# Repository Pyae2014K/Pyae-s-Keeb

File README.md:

# Pyae-s-Keeb

My Keeb is a 75% keyboard with a knob and via support.
The firmware was built with QMK.

It serves as a keyboard that I can use every day to type and play games.

## Features:
- EC11 Rotary Encoder for Volume
- 82 Switches for the keys
- [VIA](https://www.caniusevia.com/) support

## PCB
My PCB was made in KiCad.

Schematic

PCB

I used [Joe Scotto's](https://www.youtube.com/@joe_scotto) footprints for most of the components.

## CAD Model
Everyting fits together using 8 M3 Screws and Heatset inserts.

It has 2 different pieces, the Case

and the Plate

## Firmware
This Keeb uses [QMK](https://qmk.fm/) firmware for the code.
-82 Switches for keys
-Rotary encoder for volume

## Bom:
Here is everything needed to make my Keeb

82x Cherry MX Switches
82x DSA Keycaps
8x M3x5x4 Heatset inserts
8x M3x18mm SHCS Bolts
83x 1N4148 DO-35 Diodes.
1x EC11 Rotary Encoder
1x Raspberry Pi Pico
1x Case (2 printed parts)

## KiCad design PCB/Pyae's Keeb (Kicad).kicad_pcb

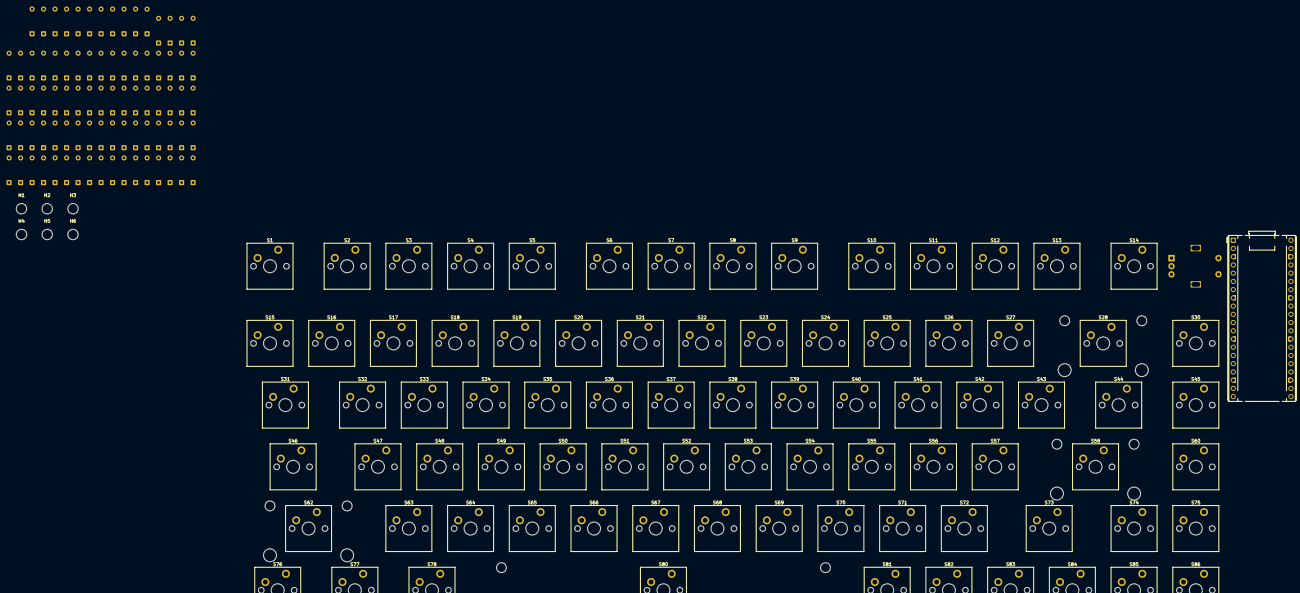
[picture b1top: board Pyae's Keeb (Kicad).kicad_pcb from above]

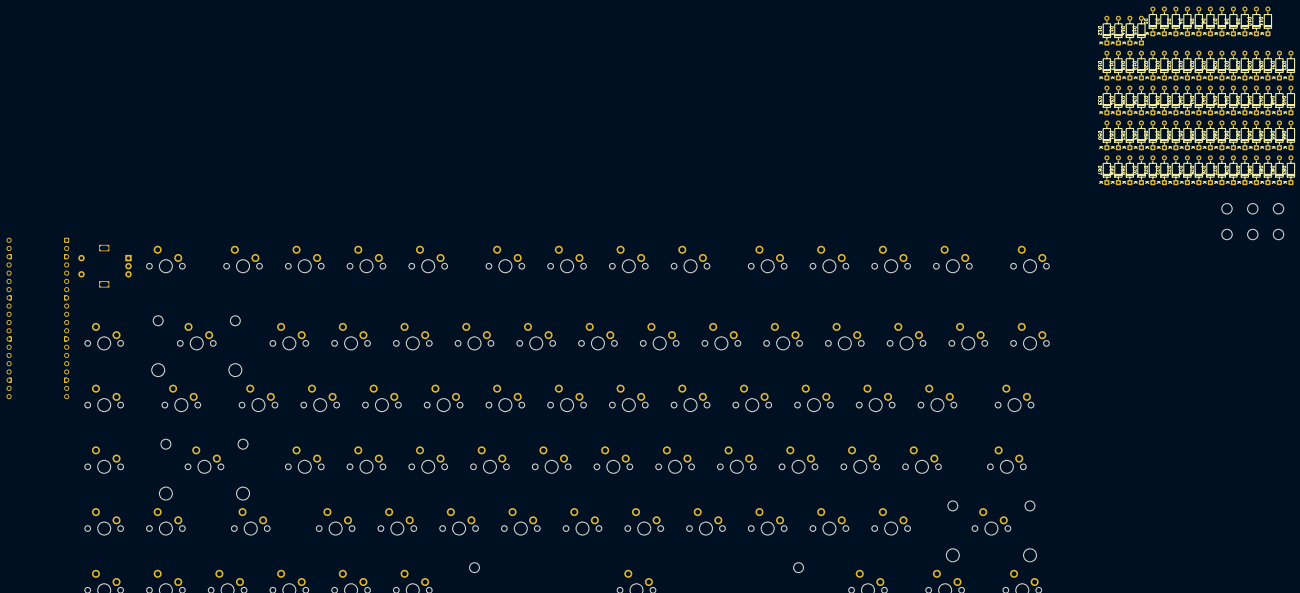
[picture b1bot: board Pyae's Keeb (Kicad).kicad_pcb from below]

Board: 2 copper layers, 177 parts (83 on the bottom side), 107 nets, no tracks yet.

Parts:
A1: RaspberryPi_Pico; RaspberryPi_Pico_Common_THT
D1, D2, D3, D4, D5, D6, D7, D8, D9, D10, D11, D12, D13, D14, D15, D16, D17, D18, D19, D20, D21, D22, D23, D24, D25, D26, D27, D28, D29, D30, D31, D32, D33, D34, D35, D36, D37, D38, D39, D40, D41, D42, D43, D44, D45, D46, D47, D48, D49, D50, D51, D52, D53, D54, D55, D56, D57, D58, D59, D60, D61, D62, D63, D64, D65, D66, D67, D68, D69, D70, D71, D72, D73, D74, D75, D76, D77, D78, D79, D80, D81, D82, D83: D_DO-35_SOD27_P7.62mm_Horizontal
H1, H2, H3, H4, H5, H6: MountingHole; MountingHole_3.2mm_M3
S1, S2, S3, S4, S5, S6, S7, S8, S9, S10, S11, S12, S13, S14, S15, S16, S17, S18, S19, S20, S21, S22, S23, S24, S25, S26, S27, S28, S30, S32, S33, S34, S35, S36, S37, S38, S39, S40, S41, S42, S43, S45, S47, S48, S49, S50, S51, S52, S53, S54, S55, S56, S57, S58, S60, S62, S63, S64, S65, S66, S67, S68, S69, S70, S71, S72, S74, S75, S80, S81, S82, S83, S84, S85, S86: MX_PCB_1.00u
S29: MX_stab; STAB_MX_2u
S31, S44: MX_PCB_1.50u
S46, S73: MX_PCB_1.75u
S59, S61: MX_stab; STAB_MX_2.25u
S76, S77, S78: MX_PCB_1.25u
S79: MX_stab; STAB_MX_6.25u
SW1: RotaryEncoder_Switch; Encoder_EC11_MX

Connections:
Col0: A1.1 (GPIO0), S1.1, S15.1, S31.1, S46.1, S62.1, S76.1
Col1: A1.2 (GPIO1), S2.1, S16.1, S32.1, S47.1, S63.1, S77.1
Col2: A1.4 (GPIO2), S3.1, S17.1, S33.1, S48.1, S64.1, S78.1
Col3: A1.5 (GPIO3), S4.1, S18.1, S34.1, S49.1, S65.1
Col4: A1.6 (GPIO4), S5.1, S19.1, S35.1, S50.1, S66.1
Col5: A1.7 (GPIO5), S6.1, S20.1, S36.1, S51.1, S67.1, S80.1
Col6: A1.9 (GPIO6), S7.1, S21.1, S37.1, S52.1, S68.1
Col7: A1.10 (GPIO7), S8.1, S22.1, S38.1, S53.1, S69.1
Col8: A1.11 (GPIO8), S9.1, S23.1, S39.1, S54.1, S70.1, S81.1
Col9: A1.12 (GPIO9), S10.1, S24.1, S40.1, S55.1, S71.1, S82.1
Col10: A1.14 (GPIO10), S11.1, S25.1, S41.1, S56.1, S72.1, S83.1
Col11: A1.15 (GPIO11), S12.1, S26.1, S42.1, S57.1, S73.1, S84.1
Col12: A1.16 (GPIO12), S13.1, S27.1, S43.1, S58.1, S74.1, S85.1
Col13: A1.17 (GPIO13), S14.1, S28.1, S44.1
Col14: A1.19 (GPIO14), S30.1, S45.1, S60.1, S75.1, S86.1, SW1.S1
GND: A1.3 (GND), A1.8 (GND), A1.13 (GND), A1.18 (GND), A1.23 (GND), A1.28 (GND), A1.38 (GND), SW1.C
unnamed: D67.2 (A), S1.2
unnamed: D68.2 (A), S15.2
unnamed: D69.2 (A), S31.2
unnamed: D70.2 (A), S46.2
unnamed: D71.2 (A), S62.2
unnamed: D72.2 (A), S76.2
unnamed: D73.2 (A), S2.2
unnamed: D74.2 (A), S16.2
unnamed: D75.2 (A), S32.2
unnamed: D76.2 (A), S47.2
unnamed: D77.2 (A), S63.2
unnamed: D78.2 (A), S77.2
unnamed: D79.2 (A), S3.2
unnamed: D80.2 (A), S17.2
unnamed: D81.2 (A), S33.2
unnamed: D82.2 (A), S48.2
unnamed: D83.2 (A), S64.2
unnamed: D50.2 (A), S78.2
unnamed: D51.2 (A), S4.2
unnamed: D52.2 (A), S18.2
unnamed: D53.2 (A), S34.2
unnamed: D54.2 (A), S49.2
unnamed: D55.2 (A), S65.2
unnamed: D56.2 (A), S5.2
unnamed: D57.2 (A), S19.2
unnamed: D58.2 (A), S35.2
unnamed: D59.2 (A), S50.2
unnamed: D60.2 (A), S66.2
unnamed: D61.2 (A), S6.2
unnamed: D62.2 (A), S20.2
unnamed: D63.2 (A), S36.2
unnamed: D64.2 (A), S51.2
unnamed: D65.2 (A), S67.2
unnamed: D66.2 (A), S80.2
unnamed: D33.2 (A), S7.2
unnamed: D34.2 (A), S21.2
unnamed: D35.2 (A), S37.2
unnamed: D36.2 (A), S52.2
unnamed: D37.2 (A), S68.2
unnamed: D38.2 (A), S8.2
unnamed: D39.2 (A), S22.2
unnamed: D40.2 (A), S38.2
unnamed: D41.2 (A), S53.2
unnamed: D42.2 (A), S69.2
unnamed: D43.2 (A), S9.2
unnamed: D44.2 (A), S23.2
unnamed: D45.2 (A), S39.2
unnamed: D46.2 (A), S54.2
unnamed: D47.2 (A), S70.2
unnamed: D48.2 (A), S81.2
unnamed: D49.2 (A), S10.2
unnamed: D16.2 (A), S24.2
unnamed: D17.2 (A), S40.2
unnamed: D18.2 (A), S55.2
unnamed: D19.2 (A), S71.2
unnamed: D20.2 (A), S82.2
unnamed: D21.2 (A), S11.2
unnamed: D22.2 (A), S25.2
unnamed: D23.2 (A), S41.2
unnamed: D24.2 (A), S56.2
unnamed: D25.2 (A), S72.2
unnamed: D26.2 (A), S83.2
unnamed: D27.2 (A), S12.2
unnamed: D28.2 (A), S26.2
unnamed: D29.2 (A), S42.2
unnamed: D30.2 (A), S57.2
unnamed: D31.2 (A), S73.2
unnamed: D32.2 (A), S84.2
unnamed: D12.2 (A), S13.2
unnamed: D13.2 (A), S27.2
unnamed: D14.2 (A), S43.2
unnamed: D15.2 (A), S58.2
unnamed: D1.2 (A), S74.2
unnamed: D2.2 (A), S85.2
unnamed: D3.2 (A), S14.2
unnamed: D4.2 (A), S28.2
unnamed: D5.2 (A), S44.2
unnamed: D7.2 (A), S30.2
unnamed: D8.2 (A), S45.2
unnamed: D9.2 (A), S60.2
unnamed: D10.2 (A), S75.2
unnamed: D11.2 (A), S86.2
Row0: A1.21 (GPIO16), D3.1 (K), D6.1 (K), D12.1 (K), D21.1 (K), D27.1 (K), D33.1 (K), D38.1 (K), D43.1 (K), D49.1 (K), D51.1 (K), D56.1 (K), D61.1 (K), D67.1 (K), D73.1 (K), D79.1 (K)
Row1: A1.22 (GPIO17), D4.1 (K), D7.1 (K), D13.1 (K), D16.1 (K), D22.1 (K), D28.1 (K), D34.1 (K), D39.1 (K), D44.1 (K), D52.1 (K), D57.1 (K), D62.1 (K), D68.1 (K), D74.1 (K), D80.1 (K)
Row2: A1.24 (GPIO18), D5.1 (K), D8.1 (K), D14.1 (K), D17.1 (K), D23.1 (K), D29.1 (K), D35.1 (K), D40.1 (K), D45.1 (K), D53.1 (K), D58.1 (K), D63.1 (K), D69.1 (K), D75.1 (K), D81.1 (K)
Row3: A1.25 (GPIO19), D9.1 (K), D15.1 (K), D18.1 (K), D24.1 (K), D30.1 (K), D36.1 (K), D41.1 (K), D46.1 (K), D54.1 (K), D59.1 (K), D64.1 (K), D70.1 (K), D76.1 (K), D82.1 (K)
Row4: A1.26 (GPIO20), D1.1 (K), D10.1 (K), D19.1 (K), D25.1 (K), D31.1 (K), D37.1 (K), D42.1 (K), D47.1 (K), D55.1 (K), D60.1 (K), D65.1 (K), D71.1 (K), D77.1 (K), D83.1 (K)
Row5: A1.27 (GPIO21), D2.1 (K), D11.1 (K), D20.1 (K), D26.1 (K), D32.1 (K), D48.1 (K), D50.1 (K), D66.1 (K), D72.1 (K), D78.1 (K)
SwB: D6.2 (A), SW1.S2
TnA: A1.20 (GPIO15), SW1.A
TnB: A1.29 (GPIO22), SW1.B

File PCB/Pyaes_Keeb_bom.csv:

Designator,Footprint,Quantity,Value,LCSC Part #
A1,RaspberryPi_Pico_Common_THT,1,RaspberryPi_Pico,
"D1, D10, D11, D12, D13, D14, D15, D16, D17, D18, D19, D2, D20, D21, D22, D23, D24, D25, D26, D27, D28, D29, D3, D30, D31, D32, D33, D34, D35, D36, D37, D38, D39, D4, D40, D41, D42, D43, D44, D45, D46, D47, D48, D49, D5, D50, D51, D52, D53, D54, D55, D56, D57, D58, D59, D6, D60, D61, D62, D63, D64, D65, D66, D67, D68, D69, D7, D70, D71, D72, D73, D74, D75, D76, D77, D78, D79, D8, D80, D81, D82, D83, D9",D_DO-35_SOD27_P7.62mm_Horizontal,83,~,
"S1, S10, S11, S12, S13, S14, S15, S16, S17, S18, S19, S2, S20, S21, S22, S23, S24, S25, S26, S27, S28, S3, S30, S32, S33, S34, S35, S36, S37, S38, S39, S4, S40, S41, S42, S43, S45, S47, S48, S49, S5, S50, S51, S52, S53, S54, S55, S56, S57, S58, S6, S60, S62, S63, S64, S65, S66, S67, S68, S69, S7, S70, S71, S72, S74, S75, S8, S80, S81, S82, S83, S84, S85, S86, S9",MX_PCB_1.00u,75,~,
S29,STAB_MX_2u,1,MX_stab,
"S31, S44",MX_PCB_1.50u,2,~,
"S46, S73",MX_PCB_1.75u,2,~,
"S59, S61",STAB_MX_2.25u,2,MX_stab,
"S76, S77, S78",MX_PCB_1.25u,3,~,
S79,STAB_MX_6.25u,1,MX_stab,
SW1,Encoder_EC11_MX,1,RotaryEncoder_Switch,
